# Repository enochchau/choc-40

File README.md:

# 40% Kailh choc v1 keyboard

Inspired by the [Contra](https://github.com/ai03-2725/Contra).

Estimated cost:
* PCB, Plate, and Base plate: $30
* Pro-Micro: $5
* keycaps: $20
* standoffs and screws: $5
* 48 Switches: $30
* diodes: $5
* reset switch: $0.30

Total: $95.30
Shipping: $20

Switches are spaced 18.55mm x 19mm apart (width x length). 
This should be large enough for any style of choc-v1 switch keycaps.
Plate spacing is 13.8mmx13.8mm.

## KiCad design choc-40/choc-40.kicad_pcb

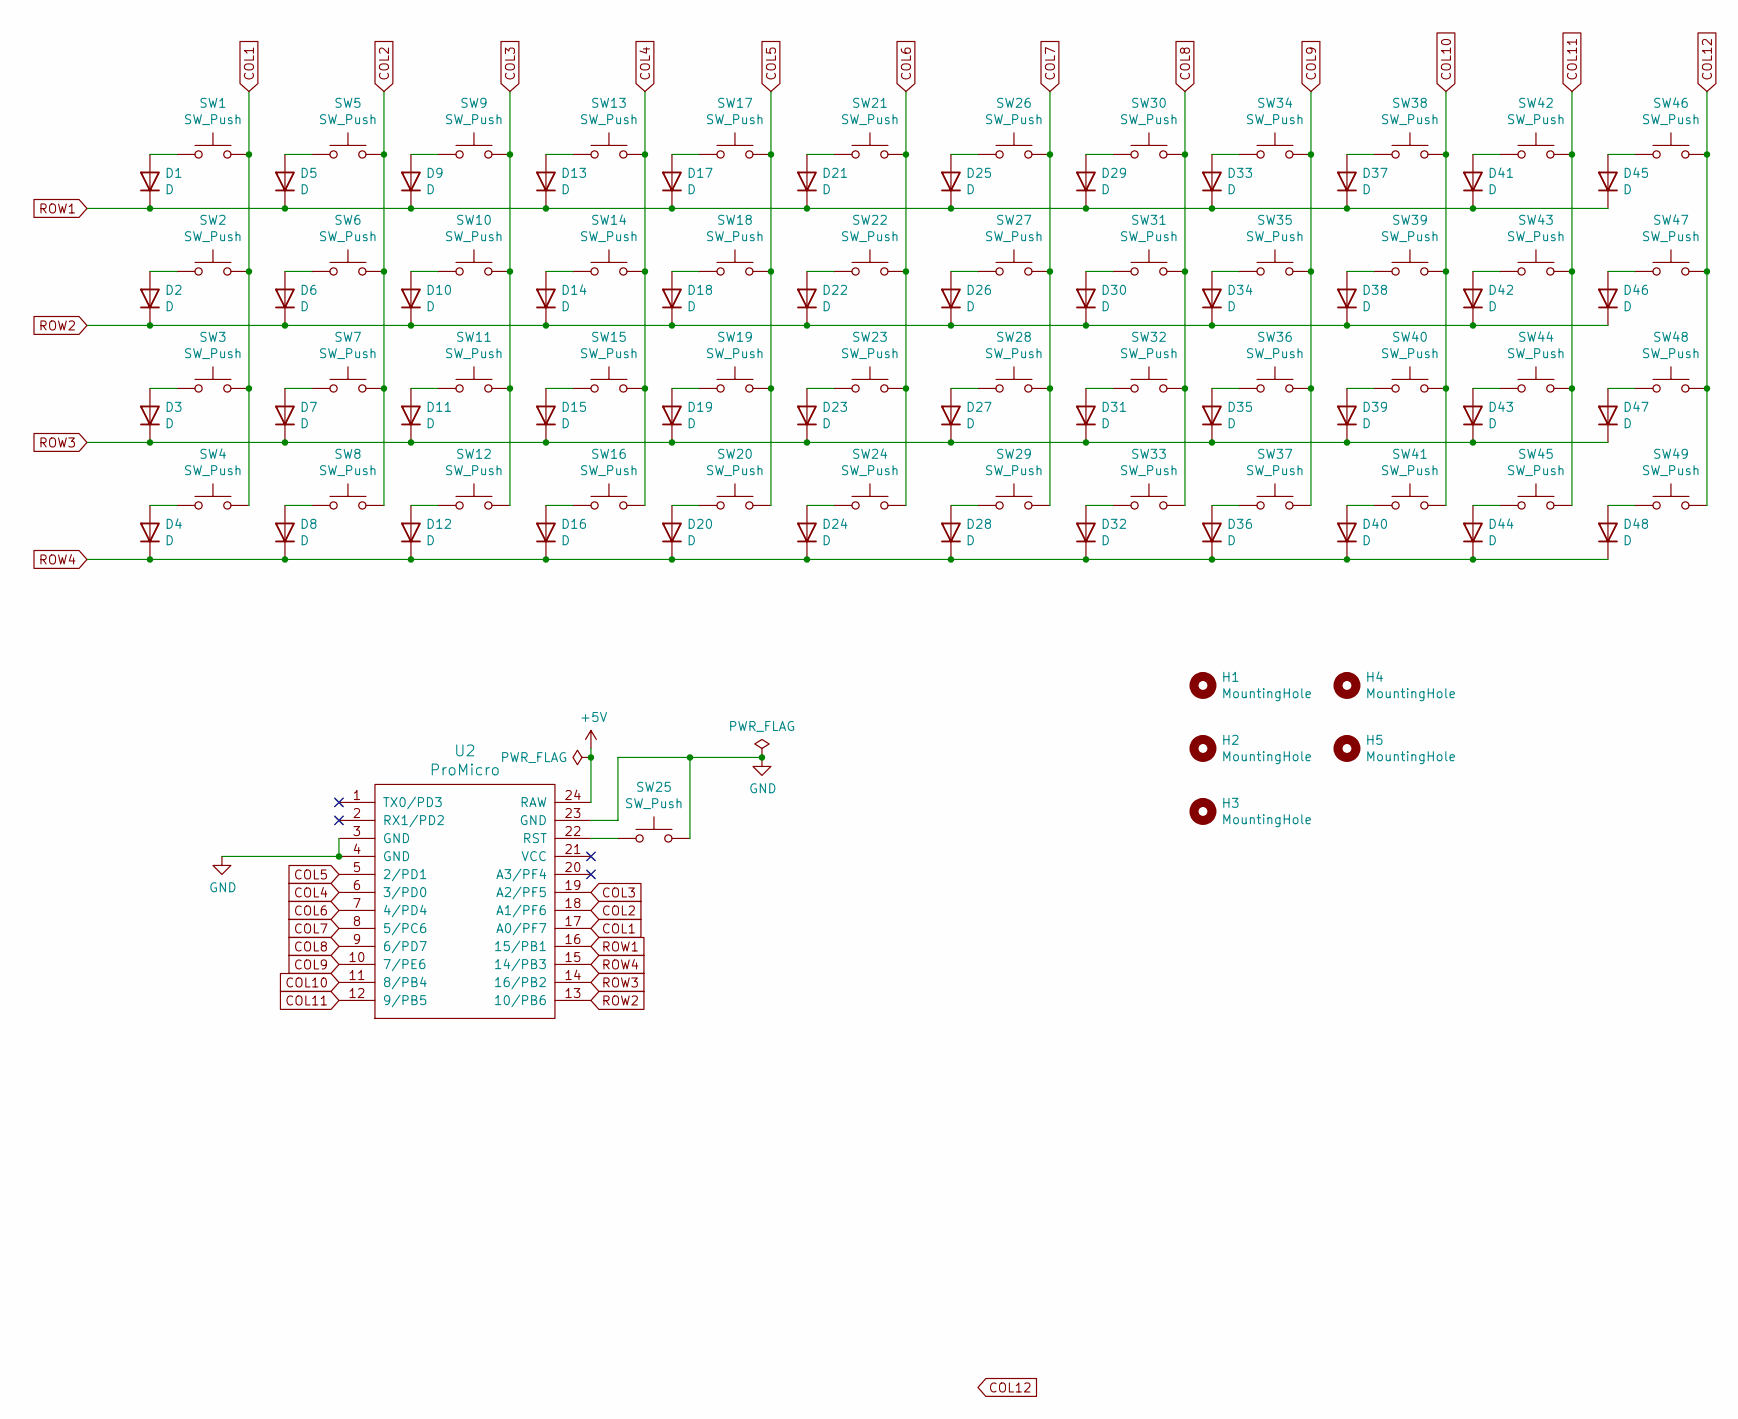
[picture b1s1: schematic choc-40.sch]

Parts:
D1, D2, D3, D4, D5, D6, D7, D8, D9, D10, D11, D12, D13, D14, D15, D16, D17, D18, D19, D20, D21, D22, D23, D24, D25, D26, D27, D28, D29, D30, D31, D32, D33, D34, D35, D36, D37, D38, D39, D40, D41, D42, D43, D44, D45, D46, D47, D48: D; D_SOD123_axial
H1, H2, H3, H4, H5: MountingHole; MountingHole_2.2mm_M2_Pad_Via
SW1, SW2, SW3, SW4, SW5, SW6, SW7, SW8, SW9, SW10, SW11, SW12, SW13, SW14, SW15, SW16, SW17, SW18, SW19, SW20, SW21, SW22, SW23, SW24, SW26, SW27, SW28, SW29, SW30, SW31, SW32, SW33, SW34, SW35, SW36, SW37, SW38, SW39, SW40, SW41, SW42, SW43, SW44, SW45, SW46, SW47, SW48, SW49: SW_Push; Kailh-PG1350-1u-NoLED
SW25: SW_Push; SW_SPST_PTS810
U2: ProMicro; ArduinoProMicro-TopSide

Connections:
COL1: SW1.2, SW2.2, SW3.2, SW4.2, U2.17 (A0/PF7)
COL2: SW5.2, SW6.2, SW7.2, SW8.2, U2.18 (A1/PF6)
COL3: SW9.2, SW10.2, SW11.2, SW12.2, U2.19 (A2/PF5)
COL4: SW13.2, SW14.2, SW15.2, SW16.2, U2.6 (3/PD0)
COL5: SW17.2, SW18.2, SW19.2, SW20.2, U2.5 (2/PD1)
COL6: SW21.2, SW22.2, SW23.2, SW24.2, U2.7 (4/PD4)
COL7: SW26.2, SW27.2, SW28.2, SW29.2, U2.8 (5/PC6)
COL8: SW30.2, SW31.2, SW32.2, SW33.2, U2.9 (6/PD7)
COL9: SW34.2, SW35.2, SW36.2, SW37.2, U2.10 (7/PE6)
COL10: SW38.2, SW39.2, SW40.2, SW41.2, U2.11 (8/PB4)
COL11: SW42.2, SW43.2, SW44.2, SW45.2, U2.12 (9/PB5)
COL12: SW46.2, SW47.2, SW48.2, SW49.2
GND: SW25.2, U2.3 (GND), U2.4 (GND), U2.23 (GND)
unnamed: D1.2 (A), SW1.1
unnamed: D2.2 (A), SW2.1
unnamed: D3.2 (A), SW3.1
unnamed: D4.2 (A), SW4.1
unnamed: D5.2 (A), SW5.1
unnamed: D6.2 (A), SW6.1
unnamed: D7.2 (A), SW7.1
unnamed: D8.2 (A), SW8.1
unnamed: D9.2 (A), SW9.1
unnamed: D10.2 (A), SW10.1
unnamed: D11.2 (A), SW11.1
unnamed: D12.2 (A), SW12.1
unnamed: D13.2 (A), SW13.1
unnamed: D14.2 (A), SW14.1
unnamed: D15.2 (A), SW15.1
unnamed: D16.2 (A), SW16.1
unnamed: D17.2 (A), SW17.1
unnamed: D18.2 (A), SW18.1
unnamed: D19.2 (A), SW19.1
unnamed: D20.2 (A), SW20.1
unnamed: D21.2 (A), SW21.1
unnamed: D22.2 (A), SW22.1
unnamed: D23.2 (A), SW23.1
unnamed: D24.2 (A), SW24.1
unnamed: D25.2 (A), SW26.1
unnamed: D26.2 (A), SW27.1
unnamed: D27.2 (A), SW28.1
unnamed: D28.2 (A), SW29.1
unnamed: D29.2 (A), SW30.1
unnamed: D30.2 (A), SW31.1
unnamed: D31.2 (A), SW32.1
unnamed: D32.2 (A), SW33.1
unnamed: D33.2 (A), SW34.1
unnamed: D34.2 (A), SW35.1
unnamed: D35.2 (A), SW36.1
unnamed: D36.2 (A), SW37.1
unnamed: D37.2 (A), SW38.1
unnamed: D38.2 (A), SW39.1
unnamed: D39.2 (A), SW40.1
unnamed: D40.2 (A), SW41.1
unnamed: D41.2 (A), SW42.1
unnamed: D42.2 (A), SW43.1
unnamed: D43.2 (A), SW44.1
unnamed: D44.2 (A), SW45.1
unnamed: D45.2 (A), SW46.1
unnamed: D46.2 (A), SW47.1
unnamed: D47.2 (A), SW48.1
unnamed: D48.2 (A), SW49.1
unnamed: SW25.1, U2.22 (RST)
ROW1: D1.1 (K), D5.1 (K), D9.1 (K), D13.1 (K), D17.1 (K), D21.1 (K), D25.1 (K), D29.1 (K), D33.1 (K), D37.1 (K), D41.1 (K), D45.1 (K), U2.16 (15/PB1)
ROW2: D2.1 (K), D6.1 (K), D10.1 (K), D14.1 (K), D18.1 (K), D22.1 (K), D26.1 (K), D30.1 (K), D34.1 (K), D38.1 (K), D42.1 (K), D46.1 (K), U2.13 (10/PB6)
ROW3: D3.1 (K), D7.1 (K), D11.1 (K), D15.1 (K), D19.1 (K), D23.1 (K), D27.1 (K), D31.1 (K), D35.1 (K), D39.1 (K), D43.1 (K), D47.1 (K), U2.14 (16/PB2)
ROW4: D4.1 (K), D8.1 (K), D12.1 (K), D16.1 (K), D20.1 (K), D24.1 (K), D28.1 (K), D32.1 (K), D36.1 (K), D40.1 (K), D44.1 (K), D48.1 (K), U2.15 (14/PB3)

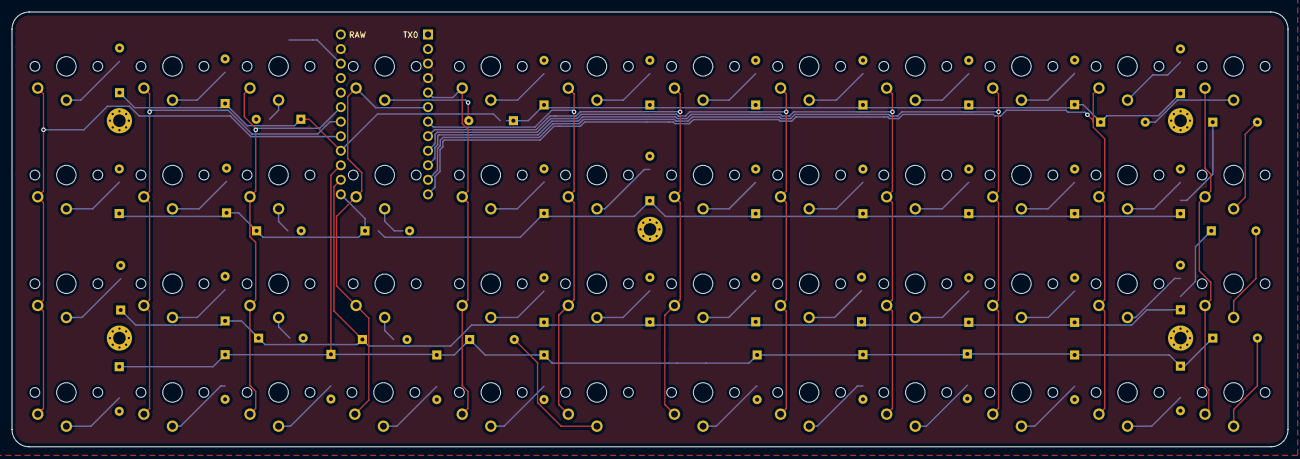
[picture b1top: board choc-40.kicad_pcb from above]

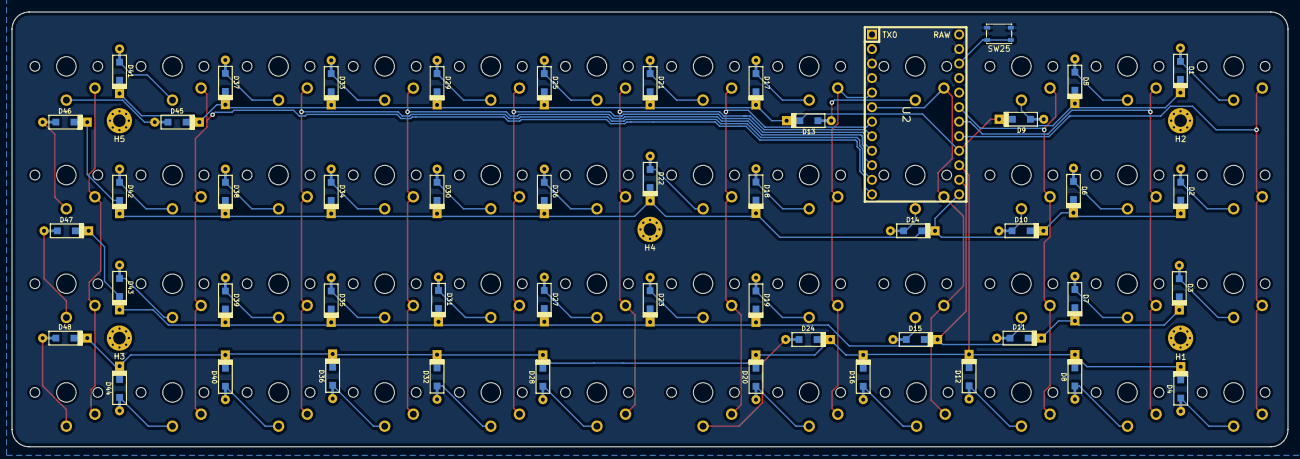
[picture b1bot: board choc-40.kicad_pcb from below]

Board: 2 copper layers, 223.1 x 76.0 mm, 103 parts (55 on the bottom side), 66 nets.

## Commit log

2021-03-20 init
2021-03-20 cleaning up lib
2021-03-20 readme
2021-03-20 remove temp cad files
2021-03-20 adding gerbers
2021-03-23 adding 2u middle key option
2021-03-23 adding base and plate
2021-03-23 forgot to connect a trace
2021-03-24 removing 2u optional layout
2021-03-24 updating plate to 13.8x13.8mm
